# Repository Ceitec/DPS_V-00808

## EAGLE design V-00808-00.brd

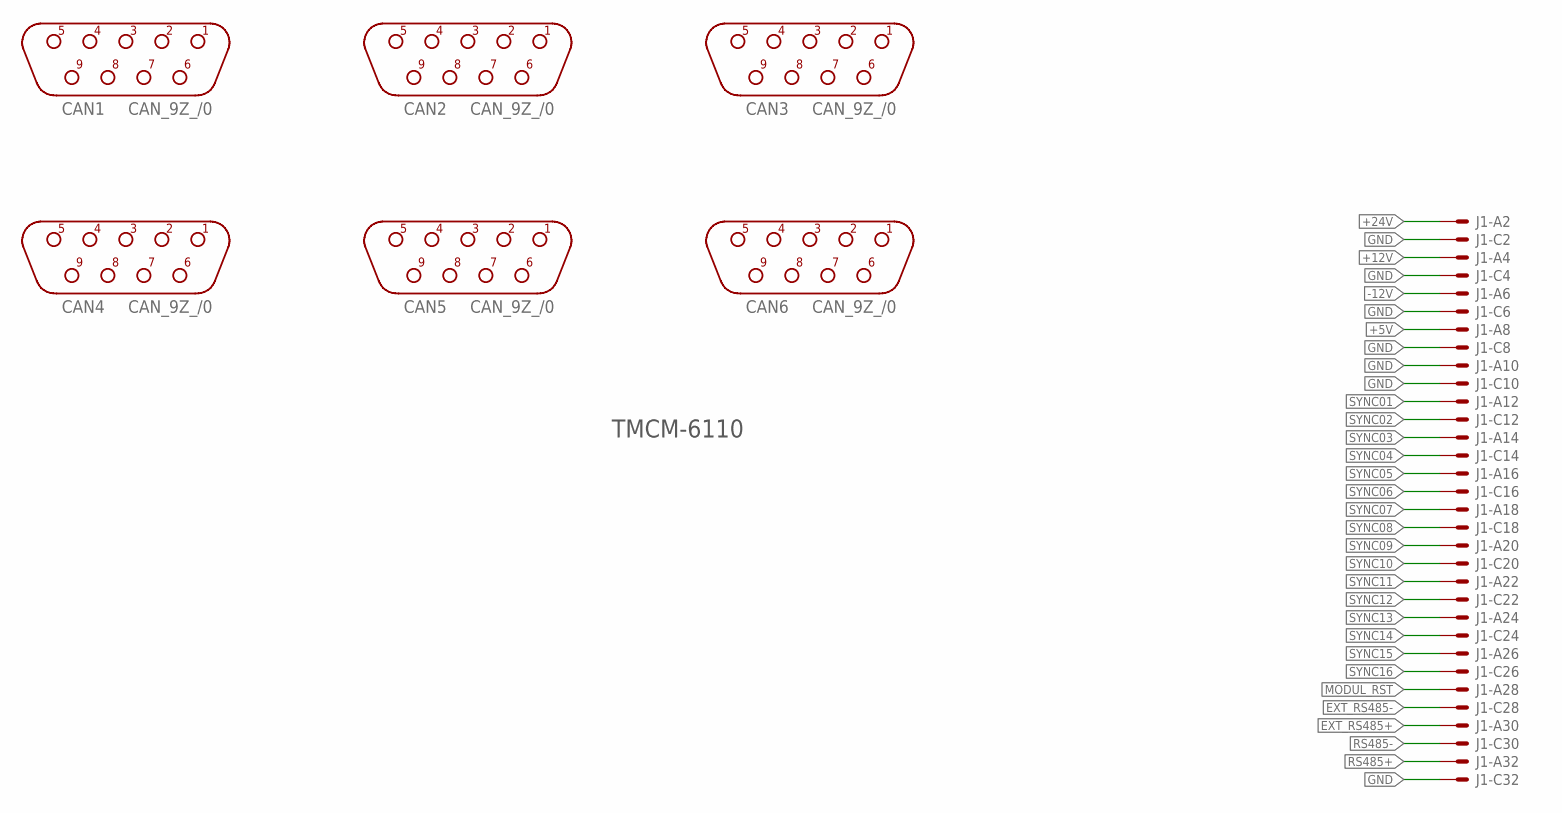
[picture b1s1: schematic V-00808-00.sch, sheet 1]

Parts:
CAN1, CAN2, CAN3, CAN4, CAN5, CAN6: CAN_9Z_/0; CAN9Z
J1: VG32SP; VG32P

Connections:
+5V: J1.A8 (MS); also elsewhere on the board
+12V: J1.A4 (MS)
+24V: J1.A2 (MS)
-12V: J1.A6 (MS)
EXT_RS485+: J1.A30 (MS)
EXT_RS485-: J1.C28 (MS)
GND: J1.A10 (MS), J1.C2 (MS), J1.C4 (MS), J1.C6 (MS), J1.C8 (MS), J1.C10 (MS), J1.C32 (MSV); also elsewhere on the board
MODUL_RST: J1.A28 (MS); also elsewhere on the board
RS485+: J1.A32 (MS)
RS485-: J1.C30 (MS)
SYNC01: J1.A12 (MS)
SYNC02: J1.C12 (MS)
SYNC03: J1.A14 (MS)
SYNC04: J1.C14 (MS)
SYNC05: J1.A16 (MS)
SYNC06: J1.C16 (MS)
SYNC07: J1.A18 (MS)
SYNC08: J1.C18 (MS)
SYNC09: J1.A20 (MS)
SYNC10: J1.C20 (MS)
SYNC11: J1.A22 (MS)
SYNC12: J1.C22 (MS)
SYNC13: J1.A24 (MS)
SYNC14: J1.C24 (MS)
SYNC15: J1.A26 (MS)
SYNC16: J1.C26 (MS)

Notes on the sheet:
TMCM-6110

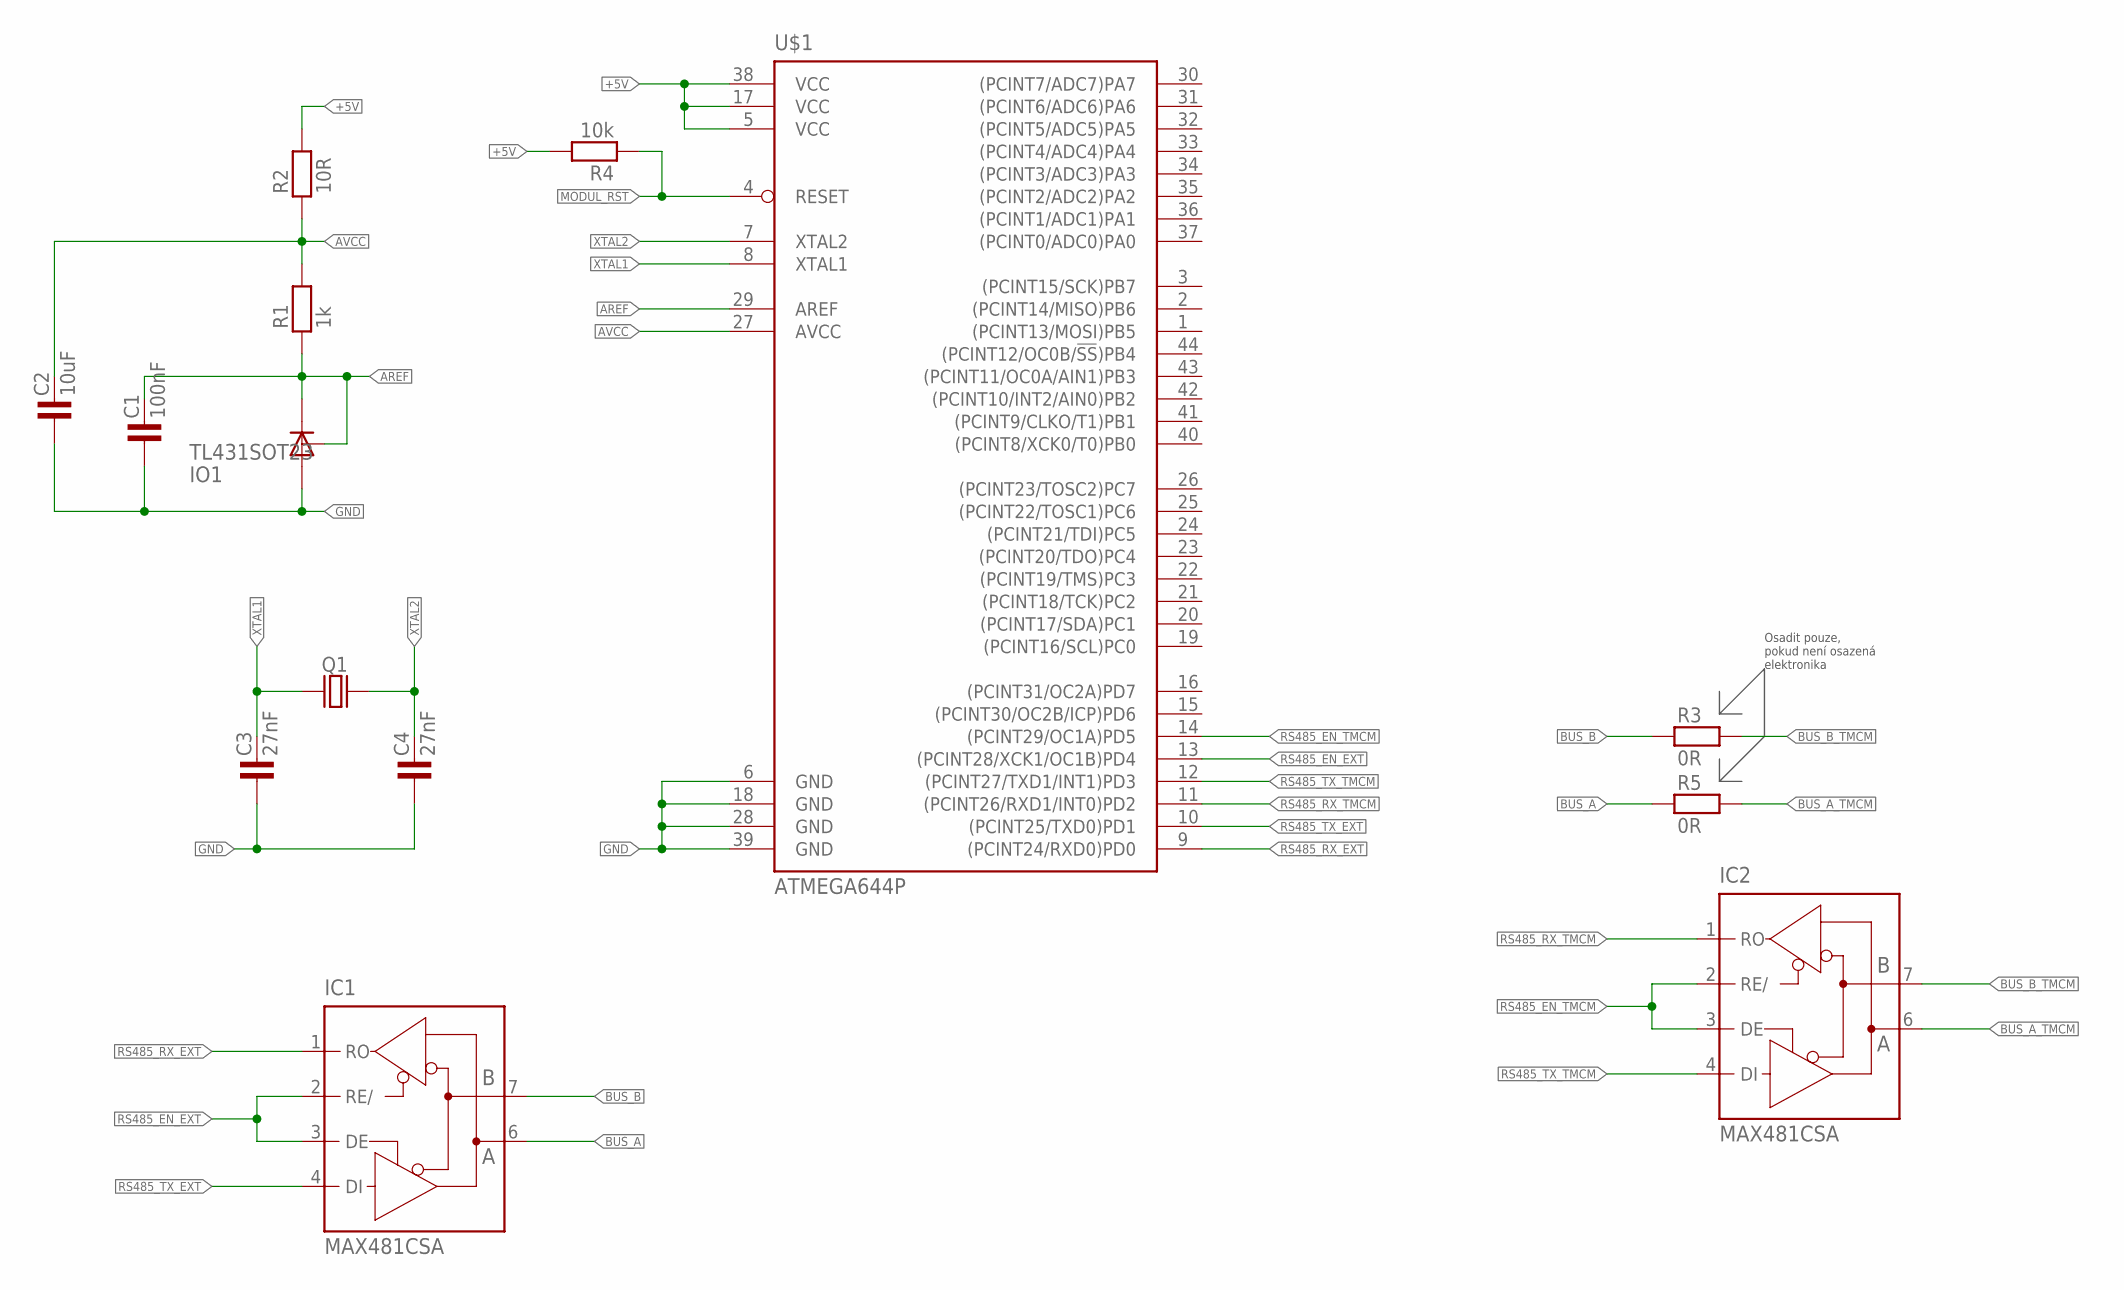
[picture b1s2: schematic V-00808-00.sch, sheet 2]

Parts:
C1: 100nF; 1206
C2: 10uF; 1206
C3, C4: 27nF; 0805
IC1, IC2: MAX481CSA; SO08
IO1: TL431SOT23; SOT23
Q1: Q_HC-49U; HC-49U
R1: 1k; 1206
R2: 10R; 1206
R3, R5: 0R; 1206
R4: 10k; 1206
U$1: ATMEGA644P; TQFP44

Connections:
+5V: R2.2, R4.2, U$1.5 (VCC), U$1.17 (VCC), U$1.38 (VCC); also elsewhere on the board
AREF: C1.2, IO1.1 (C), IO1.2 (R), R1.1, U$1.29 (AREF)
AVCC: C2.2, R1.2, R2.1, U$1.27 (AVCC)
BUS_A: IC1.6 (A), R5.1
BUS_A_TMCM: IC2.6 (A), R5.2
BUS_B: IC1.7 (B), R3.1
BUS_B_TMCM: IC2.7 (B), R3.2
GND: C1.1, C2.1, C3.1, C4.1, IC1.5 (GND), IC2.5 (GND), IO1.3 (A), U$1.6 (GND), U$1.18 (GND), U$1.28 (GND), U$1.39 (GND); also elsewhere on the board
MODUL_RST: R4.1, U$1.4 (RESET); also elsewhere on the board
RS485_EN_EXT: IC1.2 (RE/), IC1.3 (DE), U$1.13 ((PCINT28/XCK1/OC1B)PD4)
RS485_EN_TMCM: IC2.2 (RE/), IC2.3 (DE), U$1.14 ((PCINT29/OC1A)PD5)
RS485_RX_EXT: IC1.1 (RO), U$1.9 ((PCINT24/RXD0)PD0)
RS485_RX_TMCM: IC2.1 (RO), U$1.11 ((PCINT26/RXD1/INT0)PD2)
RS485_TX_EXT: IC1.4 (DI), U$1.10 ((PCINT25/TXD0)PD1)
RS485_TX_TMCM: IC2.4 (DI), U$1.12 ((PCINT27/TXD1/INT1)PD3)
VCC: IC1.8 (VCC), IC2.8 (VCC)
XTAL1: C3.2, Q1.1, U$1.8 (XTAL1)
XTAL2: C4.2, Q1.2, U$1.7 (XTAL2)

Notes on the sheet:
Osadit pouze, pokud není osazená elektronika

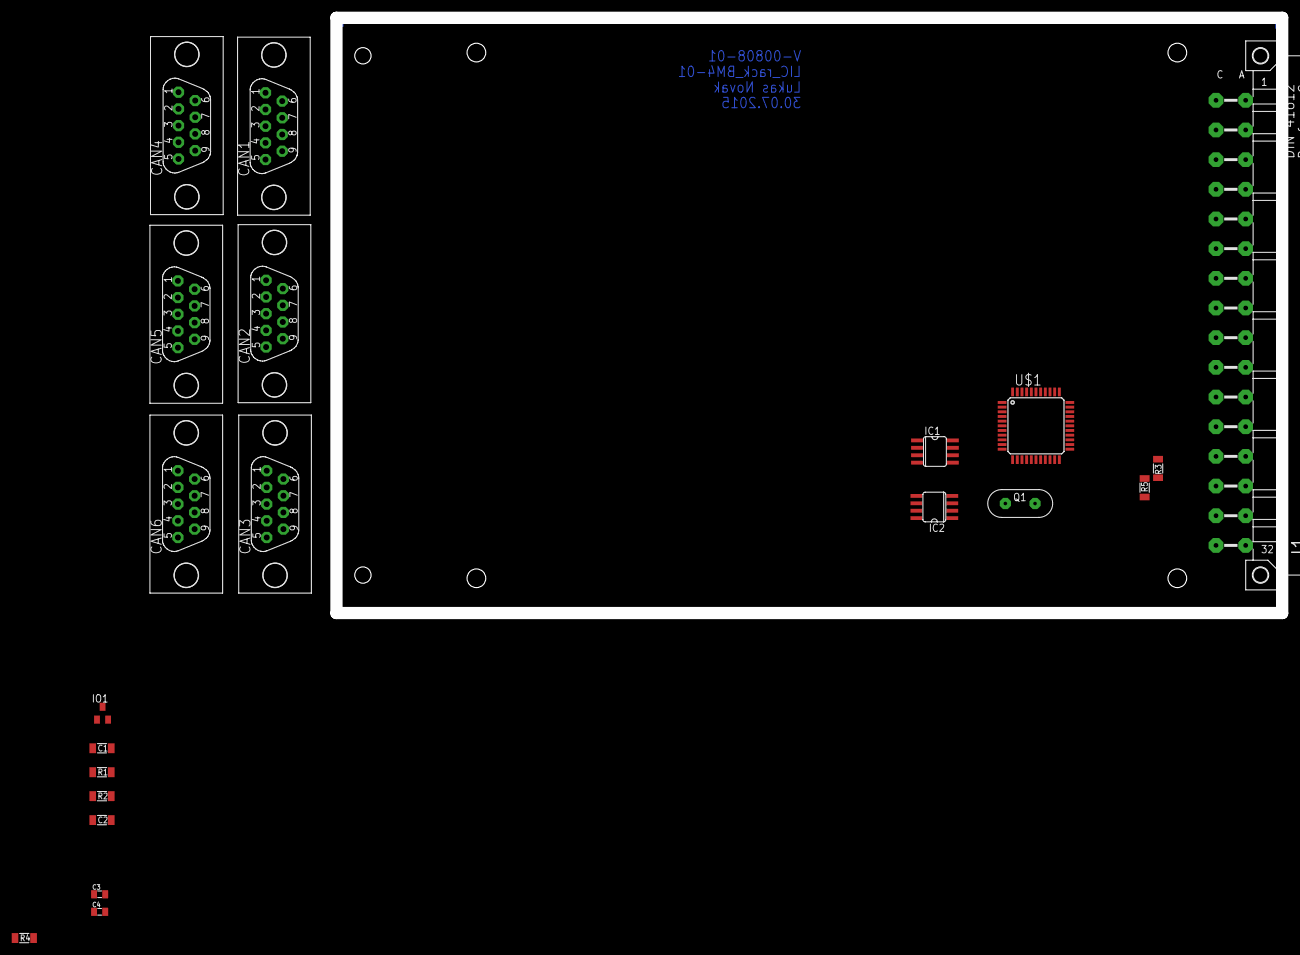
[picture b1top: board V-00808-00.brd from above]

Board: 2 copper layers, 162.0 x 102.0 mm, 21 parts (0 on the bottom side), 18 nets.

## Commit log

2016-01-21 :tada: Added .gitattributes & .gitignore files
2016-01-21 v.1.0.0
    BM6

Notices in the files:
parts and their libraries:
Copyright (C) PaJa 2011-2014
Copyright (C) PaJa 2001-2014
